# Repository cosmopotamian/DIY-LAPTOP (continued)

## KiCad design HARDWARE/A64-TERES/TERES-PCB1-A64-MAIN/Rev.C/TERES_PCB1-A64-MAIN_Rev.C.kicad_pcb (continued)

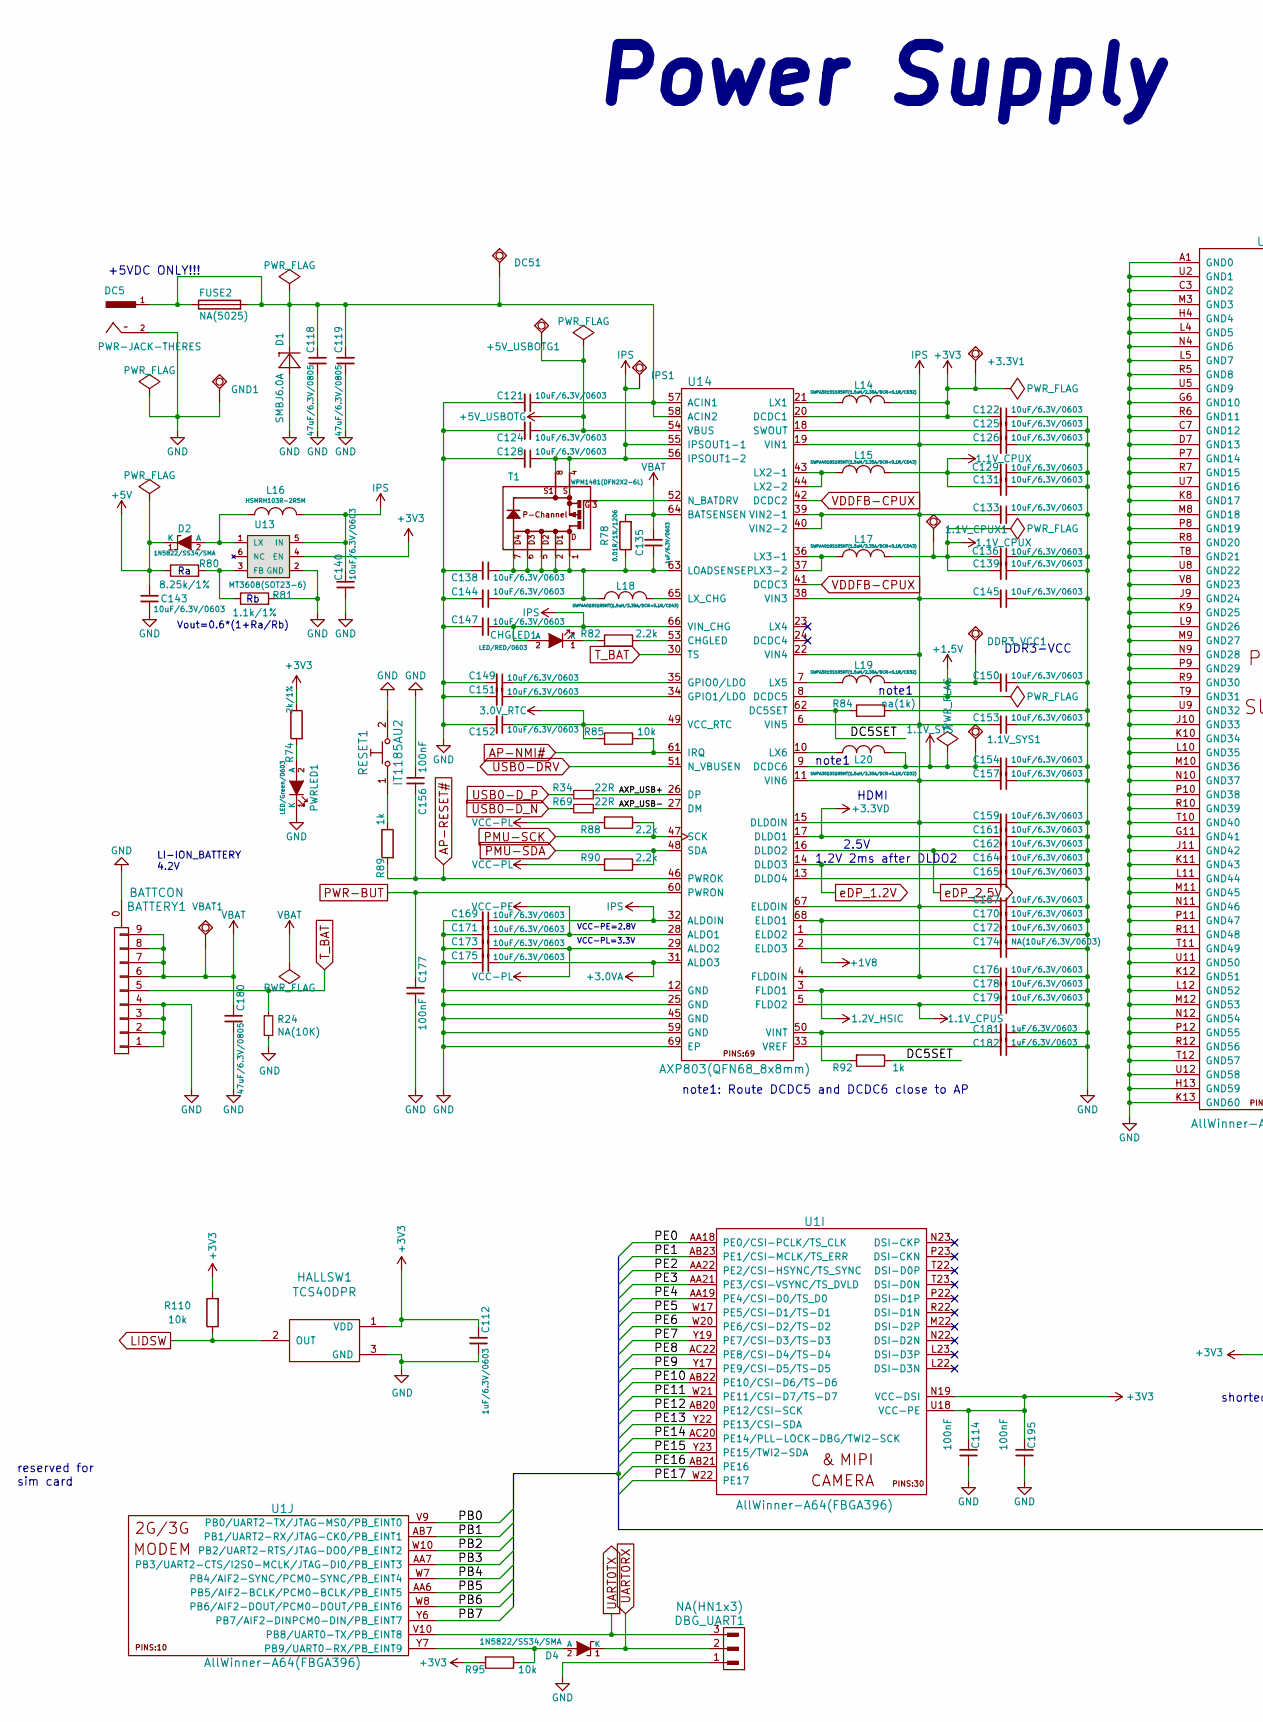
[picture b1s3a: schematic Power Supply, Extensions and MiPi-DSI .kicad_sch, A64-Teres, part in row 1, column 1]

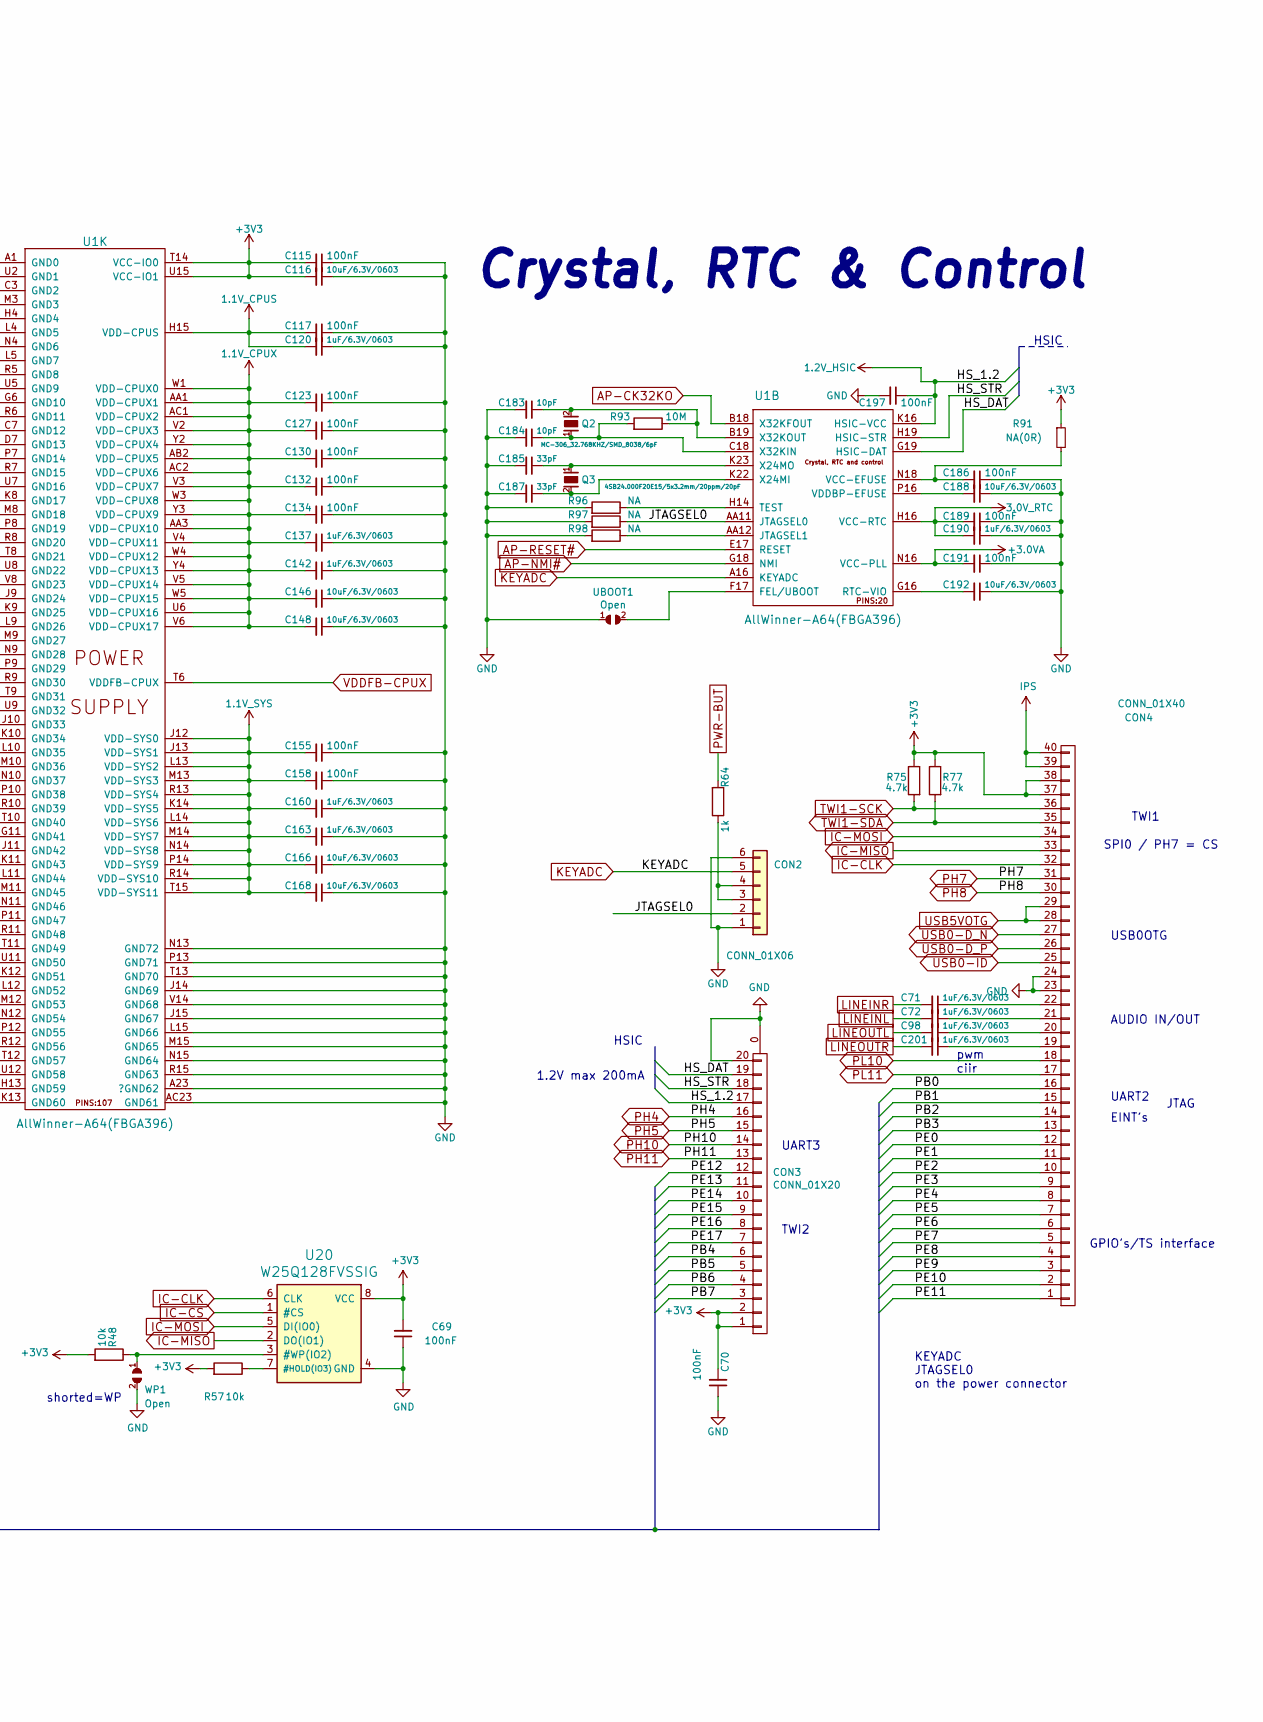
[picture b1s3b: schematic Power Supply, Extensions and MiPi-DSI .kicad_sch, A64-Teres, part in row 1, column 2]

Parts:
1.1V_CPUX1, 1.1V_SYS1: TESTPAD; TESTPAD_40-ROUND
+3.3V1: TESTPAD; TESTPAD_40-ROUND
+5V_USBOTG1: +5V_USBOTG; TESTPAD_40-ROUND
BATTERY1: BATTCON; BATCONN-TERES
C69, C70, C114, C115, C117, C123, C127, C130, C132, C134, C155, C156, C158, C177, C186, C189, C191, C195, C197: 100nF; C_0402_5MIL_DWS
C71, C72, C98, C112, C120, C135, C137, C142, C160, C163, C181, C182, C190, C201: 1uF/6.3V/0603; C_0603_5MIL_DWS
C116, C121, C122, C124, C125, C126, C128, C129, C131, C133, C136, C138, C139, C140, C143, C144, C145, C146, C147, C148, C149, C150, C151, C152, C153, C154, C157, C159, C161, C162, C164, C165, C166, C167, C168, C169, C170, C171, C172, C173, C175, C176, C178, C179, C188, C192: 10uF/6.3V/0603; C_0603_5MIL_DWS
C118, C119, C180: 47uF/6.3V/0805; C_0805_5MIL_DWS
C174: NA(10uF/6.3V/0603); C_0603_5MIL_DWS
C183, C184: 10pF; C_0402_5MIL_DWS
C185, C187: 33pF; C_0402_5MIL_DWS
CHGLED1: LED/RED/0603; LED_0603_KA
CON2: CONN_01X06; FLEXCON-0.5-6
CON3: CONN_01X20; FPV-WZA21-20-LF
CON4: CONN_01X40; FPV-WZA21-40-LF
D1: SMBJ6.0A; DO214AA
D2, D4: 1N5822/SS34/SMA; SMA-KA
DBG_UART1: NA(HN1x3); HN1x3(SMD)
DC5: PWR-JACK-THERES; DC-055-TERES
DC51: TESTPAD; TESTPAD_40-ROUND
DDR3_VCC1: TESTPAD; TESTPAD_40-ROUND
FUSE2: NA(5025); FUSE-5025
GND1: TESTPAD; TESTPAD_40-ROUND
HALLSW1: TCS40DPR; SOT23
IPS1: TESTPAD; TESTPAD_40-ROUND
L14, L19, L20: SWPA3015S1R5NT(1.5uH/2.30A/DCR<0.1R/CD32); CD32
L15, L17, L18: SWPA4018S1R5NT(1.5uH/3.35A/DCR<0.1R/CD43); CD42(43)
L16: HSMRH103R-2R5M; HSMRH103R
PWRLED1: LED/Green/0603; LED_0603_KA
Q2: MC-306_32.768KHZ/SMD_8038/6pF; MC306-HS
Q3: 4SB24.000F20E15/5x3.2mm/20ppm/20pF; Q5x3.25
R24: NA(10K); R_0402_5MIL_DWS
R34, R69: 22R; R_0402_5MIL_DWS
R48, R57, R85, R95, R110: 10k; R_0402_5MIL_DWS
R64, R89, R92: 1k; R_0402_5MIL_DWS
R74: 2k/1%; R_0402_5MIL_DWS
R75, R77: 4.7k; R_0402_5MIL_DWS
R78: 0.01R/1%/1206; R_1206_5MIL_DWS
R80: 8.25k/1%; R_0402_5MIL_DWS
R81: 1.1k/1%; R_0402_5MIL_DWS
R82, R88, R90: 2.2k; R_0402_5MIL_DWS
R84: na(1k); R_0402_5MIL_DWS
R91: NA(0R); R_0402_5MIL_DWS
R93: 10M; R_0402_5MIL_DWS
R96, R97, R98: NA; R_0402_5MIL_DWS
RESET1: IT1185AU2; uTACTIL
T1: WPM1481(DFN2X2-6L); DFN2x2-6L
U1: AllWinner-A64(FBGA396); FBGA396
U13: MT3608(SOT23-6); SOT23-6
U14: AXP803(QFN68_8x8mm); QFN68
U20: W25Q128FVSSIG; SO-8_208mil
UBOOT1: Open; SJ
VBAT1: TESTPAD; TESTPAD_40-ROUND
WP1: Open; SJ

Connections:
1.1V_CPUS: C117.2, C120.2, C179.2, U1.H15 (VDD-CPUS), U14.5 (FLDO2)
1.1V_CPUX: 1.1V_CPUX1.1, C123.2, C127.2, C129.2, C130.2, C131.2, C132.2, C134.2, C136.2, C137.2, C139.2, C142.2, C146.2, C148.2, L15.2, L17.2, U1.AA1 (VDD-CPUX1), U1.AA3 (VDD-CPUX10), U1.AB2 (VDD-CPUX5), U1.AC1 (VDD-CPUX2), U1.AC2 (VDD-CPUX6), U1.U6 (VDD-CPUX16), U1.V2 (VDD-CPUX3), U1.V3 (VDD-CPUX7), U1.V4 (VDD-CPUX11), U1.V5 (VDD-CPUX14), U1.V6 (VDD-CPUX17), U1.W1 (VDD-CPUX0), U1.W3 (VDD-CPUX8), U1.W4 (VDD-CPUX12), U1.W5 (VDD-CPUX15), U1.Y2 (VDD-CPUX4), U1.Y3 (VDD-CPUX9), U1.Y4 (VDD-CPUX13)
1.1V_SYS: 1.1V_SYS1.1, C154.2, C155.2, C158.2, C160.2, C163.2, C166.2, C168.2, L20.2, U1.J12 (VDD-SYS0), U1.J13 (VDD-SYS1), U1.K14 (VDD-SYS5), U1.L13 (VDD-SYS2), U1.L14 (VDD-SYS6), U1.M13 (VDD-SYS3), U1.M14 (VDD-SYS7), U1.N14 (VDD-SYS8), U1.P14 (VDD-SYS9), U1.R13 (VDD-SYS4), U1.R14 (VDD-SYS10), U1.T15 (VDD-SYS11), U14.9 (DCDC6)
1.2V_HSIC: C178.2, C197.1, CON3.17, U1.K16 (HSIC-VCC), U14.3 (FLDO1)
3.0V_RTC: C152.1, C189.2, C190.2, R85.2, U1.H16 (VCC-RTC), U14.49 (VCC_RTC)
+1.5V: C150.2, DDR3_VCC1.1, L19.2, U14.8 (DCDC5); also elsewhere on the board
+1V8: C170.2, U14.68 (ELDO1); also elsewhere on the board
+3.0VA: C175.1, C191.2, U1.N16 (VCC-PLL), U14.31 (ALDO3); also elsewhere on the board
+3.3VD: C161.2, U14.17 (DLDO1); also elsewhere on the board
+3V3: +3.3V1.1, C69.2, C70.2, C112.2, C114.2, C115.2, C116.2, C122.2, C195.2, CON3.1, CON3.2, CON4.37, CON4.38, HALLSW1.1 (VDD), L14.2, R48.2, R57.2, R74.1, R75.1, R77.1, R91.1, R95.2, R110.2, U1.N19 (VCC-DSI), U1.T14 (VCC-IO0), U1.U15 (VCC-IO1), U1.U18 (VCC-PE), U13.4 (EN), U14.20 (DCDC1), U20.8 (VCC); also elsewhere on the board
+5V: C143.2, D2.1 (K), R80.1; also elsewhere on the board
/Power Supply, Extensions and MiPi-DSI/AXP_USB+: R34.1, U14.26 (DP)
/Power Supply, Extensions and MiPi-DSI/AXP_USB-: R69.1, U14.27 (DM)
/Power Supply, Extensions and MiPi-DSI/DC5SET: R84.2, R92.1, U14.62 (DC5SET)
/Power Supply, Extensions and MiPi-DSI/HS_DAT: CON3.19, U1.G19 (HSIC-DAT)
/Power Supply, Extensions and MiPi-DSI/HS_STR: CON3.18, U1.H19 (HSIC-STR)
/Power Supply, Extensions and MiPi-DSI/JTAGSEL0: CON2.2, R97.1, U1.AA11 (JTAGSEL0)
/Power Supply, Extensions and MiPi-DSI/PB0: CON4.16, U1.V9 (PB0/UART2-TX/JTAG-MS0/PB_EINT0)
/Power Supply, Extensions and MiPi-DSI/PB1: CON4.15, U1.AB7 (PB1/UART2-RX/JTAG-CK0/PB_EINT1)
/Power Supply, Extensions and MiPi-DSI/PB2: CON4.14, U1.W10 (PB2/UART2-RTS/JTAG-DO0/PB_EINT2)
/Power Supply, Extensions and MiPi-DSI/PB3: CON4.13, U1.AA7 (PB3/UART2-CTS/I2S0-MCLK/JTAG-DI0/PB_EIN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)
/Power Supply, Extensions and MiPi-DSI/PB4: CON3.6, U1.W7 (PB4/AIF2-SYNC/PCM0-SYNC/PB_EINT4)
/Power Supply, Extensions and MiPi-DSI/PB5: CON3.5, U1.AA6 (PB5/AIF2-BCLK/PCM0-BCLK/PB_EINT5)
/Power Supply, Extensions and MiPi-DSI/PB6: CON3.4, U1.W8 (PB6/AIF2-DOUT/PCM0-DOUT/PB_EINT6)
/Power Supply, Extensions and MiPi-DSI/PB7: CON3.3, U1.Y6 (PB7/AIF2-DINPCM0-DIN/PB_EINT7)
/Power Supply, Extensions and MiPi-DSI/PE0: CON4.12, U1.AA18 (PE0/CSI-PCLK/TS_CLK)
/Power Supply, Extensions and MiPi-DSI/PE1: CON4.11, U1.AB23 (PE1/CSI-MCLK/TS_ERR)
/Power Supply, Extensions and MiPi-DSI/PE2: CON4.10, U1.AA22 (PE2/CSI-HSYNC/TS_SYNC)
/Power Supply, Extensions and MiPi-DSI/PE3: CON4.9, U1.AA21 (PE3/CSI-VSYNC/TS_DVLD)
/Power Supply, Extensions and MiPi-DSI/PE4: CON4.8, U1.AA19 (PE4/CSI-D0/TS_D0)
/Power Supply, Extensions and MiPi-DSI/PE5: CON4.7, U1.W17 (PE5/CSI-D1/TS-D1)
/Power Supply, Extensions and MiPi-DSI/PE6: CON4.6, U1.W20 (PE6/CSI-D2/TS-D2)
/Power Supply, Extensions and MiPi-DSI/PE7: CON4.5, U1.Y19 (PE7/CSI-D3/TS-D3)
/Power Supply, Extensions and MiPi-DSI/PE8: CON4.4, U1.AC22 (PE8/CSI-D4/TS-D4)
/Power Supply, Extensions and MiPi-DSI/PE9: CON4.3, U1.Y17 (PE9/CSI-D5/TS-D5)
/Power Supply, Extensions and MiPi-DSI/PE10: CON4.2, U1.AB22 (PE10/CSI-D6/TS-D6)
/Power Supply, Extensions and MiPi-DSI/PE11: CON4.1, U1.W21 (PE11/CSI-D7/TS-D7)
/Power Supply, Extensions and MiPi-DSI/PE12: CON3.12, U1.AB20 (PE12/CSI-SCK)
/Power Supply, Extensions and MiPi-DSI/PE13: CON3.11, U1.Y22 (PE13/CSI-SDA)
/Power Supply, Extensions and MiPi-DSI/PE14: CON3.10, U1.AC20 (PE14/PLL-LOCK-DBG/TWI2-SCK)
/Power Supply, Extensions and MiPi-DSI/PE15: CON3.9, U1.Y23 (PE15/TWI2-SDA)
/Power Supply, Extensions and MiPi-DSI/PE16: CON3.8, U1.AB21 (PE16)
/Power Supply, Extensions and MiPi-DSI/PE17: CON3.7, U1.W22 (PE17)
AP-CK32KO: U1.B18 (X32KFOUT); also elsewhere on the board
AP-NMI#: R85.1, U1.G18 (NMI), U14.61 (IRQ)
AP-RESET#: C156.2, R89.2, U1.E17 (RESET), U14.46 (PWROK)
GND: BATTERY1.0, BATTERY1.1, BATTERY1.2, BATTERY1.3, BATTERY1.4, C69.1, C70.1, C112.1, C114.1, C115.1, C116.1, C117.1, C118.1, C119.1, C120.1, C121.2, C122.1, C123.1, C124.2, C125.1, C126.1, C127.1, C128.2, C129.1, C130.1, C131.1, C132.1, C133.1, C134.1, C136.1, C137.1, C138.2, C139.1, C140.1, C142.1, C143.1, C144.2, C145.1, C146.1, C147.2, C148.1, C149.2, C150.1, C151.2, C152.2, C153.1, C154.1, C155.1, C156.1, C157.1, C158.1, C159.1, C160.1, C161.1, C162.1, C163.1, C164.1, C165.1, C166.1, C167.1, C168.1, C169.2, C170.1, C171.2, C172.1, C173.2, C174.1, C175.2, C176.1, C177.1, C178.1, C179.1, C180.1, C181.1, C182.1, C183.2, C184.2, C185.2, C186.1, C187.2, C188.1, C189.1, C190.1, C191.1, C192.1, C195.1, C197.2, CON2.0, CON2.1, CON2.6, CON3.0, CON3.20, CON4.0, CON4.23, CON4.24, D1.A, DBG_UART1.1, DC5.2 (-), GND1.1, HALLSW1.3 (GND), PWRLED1.1 (K), R24.2, R81.2, R84.1, R96.2, R97.2, R98.2, RESET1.2, U1.A1 (GND0), U1.A23 (?GND62), U1.AC23 (GND61), U1.C3 (GND2), U1.C7 (GND12), U1.D7 (GND13), U1.G6 (GND10), U1.G11 (GND41), U1.H4 (GND4), U1.H13 (GND59), U1.J9 (GND24), U1.J10 (GND33), U1.J11 (GND42), U1.J14 (GND69), U1.J15 (GND67), U1.K8 (GND17), U1.K9 (GND25), U1.K10 (GND34), U1.K11 (GND43), U1.K12 (GND51), U1.K13 (GND60), U1.L4 (GND5), U1.L5 (GND7), U1.L9 (GND26), U1.L10 (GND35), U1.L11 (GND44), U1.L12 (GND52), U1.L15 (GND66), U1.M3 (GND3), U1.M8 (GND18), U1.M9 (GND27), U1.M10 (GND36), U1.M11 (GND45), U1.M12 (GND53), U1.M15 (GND65), U1.N4 (GND6), U1.N9 (GND28), U1.N10 (GND37), U1.N11 (GND46), U1.N12 (GND54), U1.N13 (GND72), U1.N15 (GND64), U1.P7 (GND14), U1.P8 (GND19), U1.P9 (GND29), U1.P10 (GND38), U1.P11 (GND47), U1.P12 (GND55), U1.P13 (GND71), U1.R5 (GND8), U1.R6 (GND11), U1.R7 (GND15), U1.R8 (GND20), U1.R9 (GND30), U1.R10 (GND39), U1.R11 (GND48), U1.R12 (GND56), U1.R15 (GND63), U1.T8 (GND21), U1.T9 (GND31), U1.T10 (GND40), U1.T11 (GND49), U1.T12 (GND57), U1.T13 (GND70), U1.U2 (GND1), U1.U5 (GND9), U1.U7 (GND16), U1.U8 (GND22), U1.U9 (GND32), U1.U11 (GND50), U1.U12 (GND58), U1.V8 (GND23), U1.V14 (GND68), U13.2 (GND), U14.12 (GND), U14.25 (GND), U14.45 (GND), U14.59 (GND), U14.69 (EP), U20.4 (GND), UBOOT1.1, WP1.2; also elsewhere on the board
IC-CLK: CON4.32, U20.6 (CLK); also elsewhere on the board
IC-CS: U20.1 (#CS); also elsewhere on the board
IC-MISO: CON4.33, U20.2 (DO(IO1)); also elsewhere on the board
IC-MOSI: CON4.34, U20.5 (DI(IO0)); also elsewhere on the board
IPS: C126.2, C128.1, C133.2, C140.2, C145.2, C147.1, C153.2, C157.2, C159.2, C167.2, C169.1, C176.2, CHGLED1.2 (A), CON4.39, CON4.40, IPS1.1, L16.1, T1.4 (S), T1.8 (S1), U13.5 (IN), U14.4 (FLDOIN), U14.6 (VIN5), U14.11 (VIN6), U14.15 (DLDOIN), U14.19 (VIN1), U14.22 (VIN4), U14.32 (ALDOIN), U14.38 (VIN3), U14.39 (VIN2-1), U14.40 (VIN2-2), U14.55 (IPSOUT1-1), U14.56 (IPSOUT1-2), U14.66 (VIN_CHG), U14.67 (ELDOIN); also elsewhere on the board
KEYADC: CON2.5, U1.A16 (KEYADC)
LIDSW: HALLSW1.2 (OUT), R110.1; also elsewhere on the board
LINEINL: C72.2; also elsewhere on the board
LINEINR: C71.2; also elsewhere on the board
LINEOUTL: C98.2; also elsewhere on the board
LINEOUTR: C201.2; also elsewhere on the board
unnamed: C71.1, CON4.22
unnamed: C72.1, CON4.21
unnamed: C98.1, CON4.20
unnamed: C118.2, C119.2, C121.1, D1.C, DC5.1 (+), DC51.1, FUSE2.1, FUSE2.2, U14.57 (ACIN1), U14.58 (ACIN2)
unnamed: C125.2, U14.18 (SWOUT)
unnamed: C135.1, C138.1, C144.1, L18.1, R78.1, T1.1 (D), T1.2 (D1), T1.5 (D2), T1.6 (D3), T1.7 (D4), U14.63 (LOADSENSEP)
unnamed: C149.1, U14.35 (GPIO0/LDO)
unnamed: C151.1, U14.34 (GPIO1/LDO)
unnamed: C165.2, U14.13 (DLDO4)
unnamed: C172.2, U14.1 (ELDO2)
unnamed: C174.2, U14.2 (ELDO3)
unnamed: C181.2, R92.2, U14.50 (VINT)
unnamed: C182.2, U14.33 (VREF)
unnamed: C183.1, Q2.2, R93.1, U1.B19 (X32KOUT)
unnamed: C184.1, Q2.1, R93.2, U1.C18 (X32KIN)
unnamed: C185.1, Q3.1, U1.K23 (X24MO)
unnamed: C186.2, R91.2, U1.N18 (VCC-EFUSE)
unnamed: C187.1, Q3.2, U1.K22 (X24MI)
unnamed: C188.2, U1.P16 (VDDBP-EFUSE)
unnamed: C192.2, U1.G16 (RTC-VIO)
unnamed: C201.1, CON4.19
unnamed: CHGLED1.1 (K), R82.2
unnamed: CON2.3, CON2.4, R64.1
unnamed: D2.2 (A), L16.2, U13.1 (LX)
unnamed: D4.2 (A), R95.1, U1.Y7 (PB9/UART0-RX/PB_EINT9)
unnamed: L14.1, U14.21 (LX1)
unnamed: L15.1, U14.43 (LX2-1), U14.44 (LX2-2)
unnamed: L17.1, U14.36 (LX3-1), U14.37 (LX3-2)
unnamed: L18.2, U14.65 (LX_CHG)
unnamed: L19.1, U14.7 (LX5)
unnamed: L20.1, U14.10 (LX6)
unnamed: PWRLED1.2 (A), R74.2
unnamed: R48.1, U20.3 (#WP(IO2)), WP1.1
unnamed: R57.1, U20.7 (#HOLD(IO3))
unnamed: R80.2, R81.1, U13.3 (FB)
unnamed: R82.1, U14.53 (CHGLED)
unnamed: R89.1, RESET1.1
unnamed: R96.1, U1.H14 (TEST)
unnamed: R98.1, U1.AA12 (JTAGSEL1)
unnamed: T1.3 (G), U14.52 (N_BATDRV)
unnamed: U1.F17 (FEL/UBOOT), UBOOT1.2
PH4: CON3.16; also elsewhere on the board
PH5: CON3.15; also elsewhere on the board
PH7: CON4.31; also elsewhere on the board
PH8: CON4.30; also elsewhere on the board
PH10: CON3.14; also elsewhere on the board
PH11: CON3.13; also elsewhere on the board
PL10: CON4.18; also elsewhere on the board
PL11: CON4.17; also elsewhere on the board
PMU-SCK: R88.1, U14.47 (SCK); also elsewhere on the board
PMU-SDA: R90.1, U14.48 (SDA); also elsewhere on the board
PWR-BUT: C177.2, R64.2, U14.60 (PWRON)
TWI1-SCK: CON4.36, R75.2; also elsewhere on the board
TWI1-SDA: CON4.35, R77.2; also elsewhere on the board
T_BAT: BATTERY1.5, R24.1, U14.30 (TS)
UART0RX: D4.1 (K), DBG_UART1.2; also elsewhere on the board
UART0TX: DBG_UART1.3, U1.V10 (PB8/UART0-TX/PB_EINT8); also elsewhere on the board
USB0-DRV: U14.51 (N_VBUSEN); also elsewhere on the board
USB0-D_N: CON4.27, R69.2; also elsewhere on the board
USB0-D_P: CON4.26, R34.2; also elsewhere on the board
USB0-ID: CON4.25; also elsewhere on the board
USB5VOTG: +5V_USBOTG1.1, C124.1, CON4.28, CON4.29, U14.54 (VBUS); also elsewhere on the board
VBAT: BATTERY1.6, BATTERY1.7, BATTERY1.8, BATTERY1.9, C135.2, C180.2, R78.2, U14.64 (BATSENSEN), VBAT1.1
VCC-PE: C171.1, U14.28 (ALDO1)
VCC-PL: C173.1, R88.2, R90.2, U14.29 (ALDO2); also elsewhere on the board
VDDFB-CPUX: U1.T6 (VDDFB-CPUX), U14.41 (DCDC3), U14.42 (DCDC2)
eDP_1.2V: C164.2, U14.14 (DLDO3); also elsewhere on the board
eDP_2.5V: C162.2, U14.16 (DLDO2); also elsewhere on the board

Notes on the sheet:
USB0OTG
DDR3-VCC
note1
HSIC
reserved for sim card
AUDIO IN/OUT
LI-ION_BATTERY 4.2V
1.2V max 200mA
UART2
VCC-PE=2.8V
Crystal, RTC & Control
KEYADC JTAGSEL0 on the power connector
UART3
ciir
note1: Route DCDC5 and DCDC6 close to AP
JTAG
TWI2
Power Supply
pwm
shorted=WP
1.2V 2ms after DLDO2
SPI0 / PH7 = CS
Vout=0.6*(1+Ra/Rb)
HDMI
GPIO's/TS interface
TWI1
2.5V
VCC-PL=3.3V
EINT's
+5VDC ONLY!!!

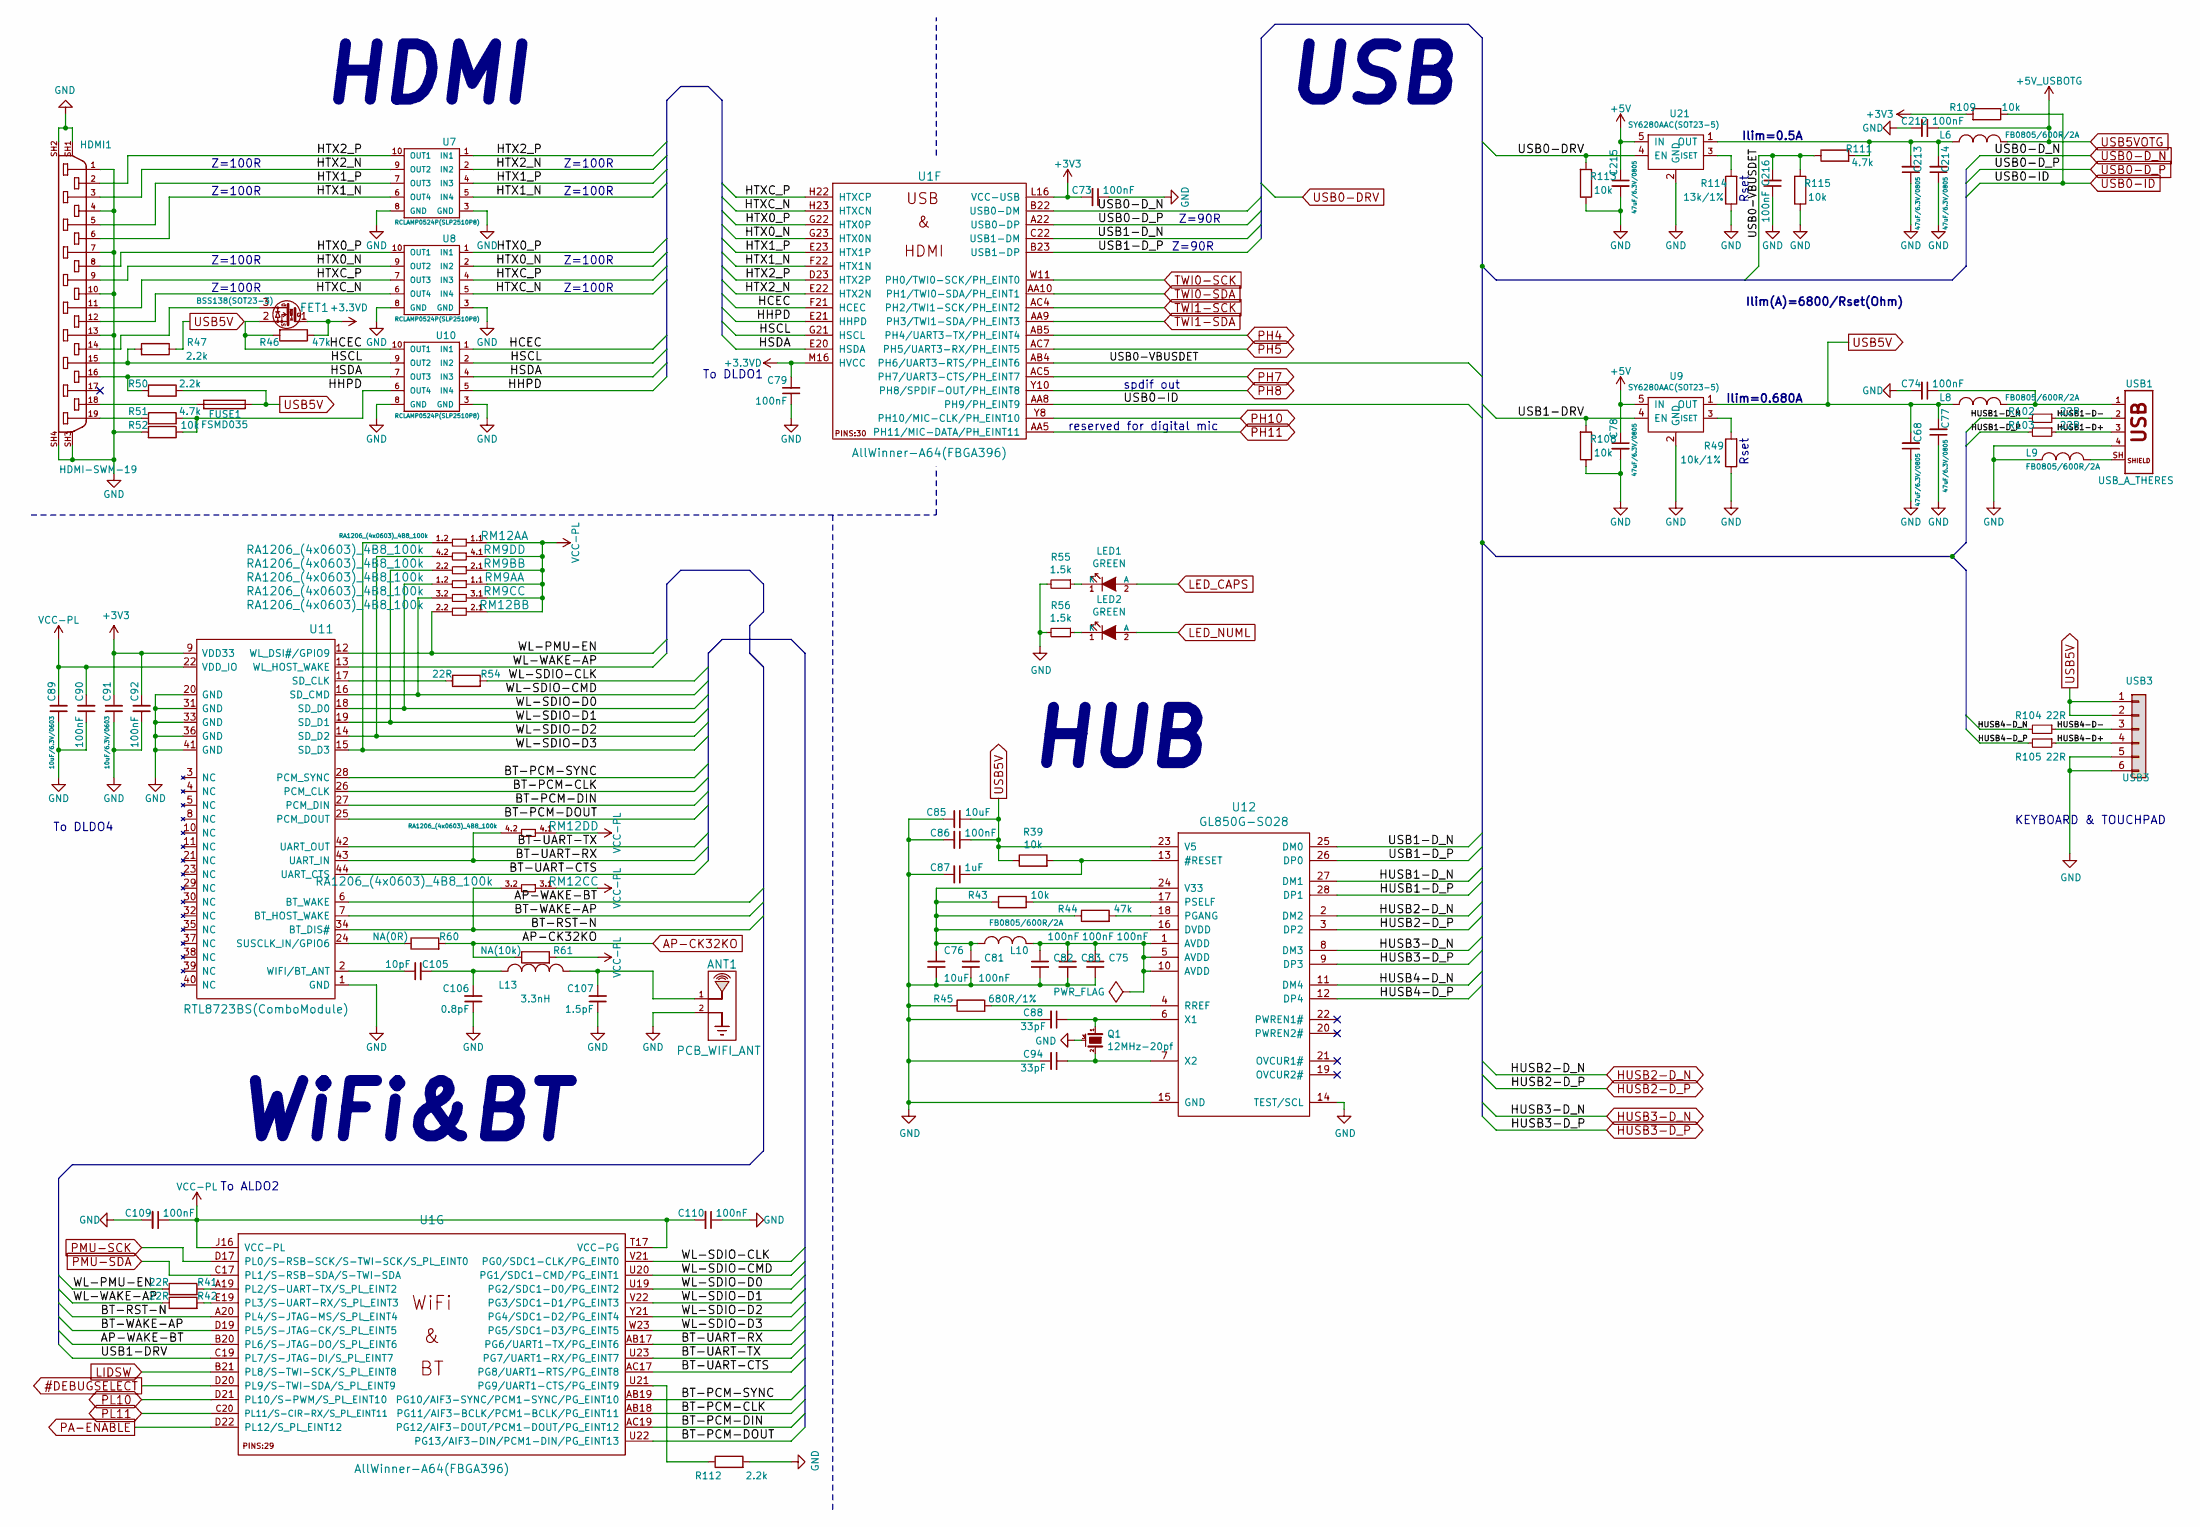
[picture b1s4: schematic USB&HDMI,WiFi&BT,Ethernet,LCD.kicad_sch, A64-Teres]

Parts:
ANT1: PCB_WIFI_ANT; U.FL-R-SMT-1
C68, C77, C78, C213, C214, C215: 47uF/6.3V/0805; C_0805_5MIL_DWS
C73, C74, C75, C79, C81, C82, C83, C86, C90, C92, C109, C110, C212, C216: 100nF; C_0402_5MIL_DWS
C76: 10uF; C_0603_5MIL_DWS
C85: 10uF; R_0603_5MIL_DWS
C87: 1uF; C_0603_5MIL_DWS
C88, C94: 33pF; C_0402_5MIL_DWS
C89, C91: 10uF/6.3V/0603; C_0603_5MIL_DWS
C105: 10pF; C_0402_5MIL_DWS
C106: 0.8pF; C_0402_5MIL_DWS
C107: 1.5pF; C_0402_5MIL_DWS
FET1: BSS138(SOT23-3); SOT23
FUSE1: FSMD035; FUSE-1206
HDMI1: HDMI-SWM-19; HDMI-MINI-TERES
L6, L8, L9, L10: FB0805/600R/2A; L_0805_5MIL_DWS
L13: 3.3nH; R_0402_5MIL_DWS
LED1, LED2: GREEN; LED_0603_KA
Q1: 12MHz-20pf; TSX-3.2x2.5mm_GND(3)
R39, R43, R52, R108, R109, R113, R115: 10k; R_0402_5MIL_DWS
R41, R42, R54, R102, R103, R104, R105: 22R; R_0402_5MIL_DWS
R44, R46: 47k; R_0402_5MIL_DWS
R45: 680R/1%; R_0603_5MIL_DWS
R47, R50, R112: 2.2k; R_0402_5MIL_DWS
R49: 10k/1%; R_0402_5MIL_DWS
R51, R111: 4.7k; R_0402_5MIL_DWS
R55, R56: 1.5k; R_0402_5MIL_DWS
R60: NA(0R); R_0402_5MIL_DWS
R61: NA(10k); R_0402_5MIL_DWS
R114: 13k/1%; R_0402_5MIL_DWS
RM9A, RM9B, RM12A, RM12B: RA1206_(4x0603)_4B8_100k; R_MATRIX_4
RM9C, RM9D, RM12C, RM12D: RA1206_(4x0603)_4B8_100k; RA1206_(4X0603)_4B8_xx
U1: AllWinner-A64(FBGA396); FBGA396
U7, U8, U10: RCLAMP0524P(SLP2510P8); SLP2510P8
U9, U21: SY6280AAC(SOT23-5); SOT-23-5
U11: RTL8723BS(ComboModule); RL-SM02BD(RTL8723BS)
U12: GL850G-SO28; SSOP28
USB1: USB_A_THERES; USB-A-TERES
USB3: USB3; FLEXCON-0.5-6

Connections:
#DEBUGSELECT: U1.D20 (PL9/S-TWI-SDA/S_PL_EINT9); also elsewhere on the board
+3.3VD: C79.2, FET1.1 (G), R46.1, U1.M16 (HVCC); also elsewhere on the board
+3V3: C73.2, C91.2, C92.2, R109.2, U1.L16 (VCC-USB), U11.9 (VDD33); also elsewhere on the board
+5V: C78.1, C215.1, U9.5 (IN), U21.5 (IN); also elsewhere on the board
/USB&HDMI,WiFi&BT,Ethernet,LCD/AP-WAKE-BT: U1.B20 (PL6/S-JTAG-DO/S_PL_EINT6), U11.6 (BT_WAKE)
/USB&HDMI,WiFi&BT,Ethernet,LCD/BT-PCM-CLK: U1.AB18 (PG11/AIF3-BCLK/PCM1-BCLK/PG_EINT11), U11.26 (PCM_CLK)
/USB&HDMI,WiFi&BT,Ethernet,LCD/BT-PCM-DIN: U1.AC19 (PG12/AIF3-DOUT/PCM1-DOUT/PG_EINT12), U11.27 (PCM_DIN)
/USB&HDMI,WiFi&BT,Ethernet,LCD/BT-PCM-DOUT: U1.U22 (PG13/AIF3-DIN/PCM1-DIN/PG_EINT13), U11.25 (PCM_DOUT)
/USB&HDMI,WiFi&BT,Ethernet,LCD/BT-PCM-SYNC: U1.AB19 (PG10/AIF3-SYNC/PCM1-SYNC/PG_EINT10), U11.28 (PCM_SYNC)
/USB&HDMI,WiFi&BT,Ethernet,LCD/BT-RST-N: RM12C.3.2, U1.A20 (PL4/S-JTAG-MS/S_PL_EINT4), U11.34 (BT_DIS#); also elsewhere on the board
/USB&HDMI,WiFi&BT,Ethernet,LCD/BT-UART-CTS: U1.AC17 (PG8/UART1-RTS/PG_EINT8), U11.44 (UART_CTS)
/USB&HDMI,WiFi&BT,Ethernet,LCD/BT-UART-RX: RM12D.4.2, U1.AB17 (PG6/UART1-TX/PG_EINT6), U11.43 (UART_IN); also elsewhere on the board
/USB&HDMI,WiFi&BT,Ethernet,LCD/BT-UART-TX: U1.U23 (PG7/UART1-RX/PG_EINT7), U11.42 (UART_OUT)
/USB&HDMI,WiFi&BT,Ethernet,LCD/BT-WAKE-AP: U1.D19 (PL5/S-JTAG-CK/S_PL_EINT5), U11.7 (BT_HOST_WAKE)
/USB&HDMI,WiFi&BT,Ethernet,LCD/HCEC: FET1.2 (S), R46.2, U1.F21 (HCEC), U10.1 (IN1), U10.10 (OUT1)
/USB&HDMI,WiFi&BT,Ethernet,LCD/HHPD: R51.1, R52.1, U1.E21 (HHPD), U10.5 (IN4), U10.6 (OUT4)
/USB&HDMI,WiFi&BT,Ethernet,LCD/HSCL: HDMI1.15, R47.2, U1.G21 (HSCL), U10.2 (IN2), U10.9 (OUT2)
/USB&HDMI,WiFi&BT,Ethernet,LCD/HSDA: HDMI1.16, R50.2, U1.E20 (HSDA), U10.4 (IN3), U10.7 (OUT3)
/USB&HDMI,WiFi&BT,Ethernet,LCD/HTX0_N: HDMI1.9, U1.G23 (HTX0N), U8.2 (IN2), U8.9 (OUT2)
/USB&HDMI,WiFi&BT,Ethernet,LCD/HTX0_P: HDMI1.8, U1.G22 (HTX0P), U8.1 (IN1), U8.10 (OUT1)
/USB&HDMI,WiFi&BT,Ethernet,LCD/HTX1_N: HDMI1.6, U1.F22 (HTX1N), U7.5 (IN4), U7.6 (OUT4)
/USB&HDMI,WiFi&BT,Ethernet,LCD/HTX1_P: HDMI1.5, U1.E23 (HTX1P), U7.4 (IN3), U7.7 (OUT3)
/USB&HDMI,WiFi&BT,Ethernet,LCD/HTX2_N: HDMI1.3, U1.E22 (HTX2N), U7.2 (IN2), U7.9 (OUT2)
/USB&HDMI,WiFi&BT,Ethernet,LCD/HTX2_P: HDMI1.2, U1.D23 (HTX2P), U7.1 (IN1), U7.10 (OUT1)
/USB&HDMI,WiFi&BT,Ethernet,LCD/HTXC_N: HDMI1.12, U1.H23 (HTXCN), U8.5 (IN4), U8.6 (OUT4)
/USB&HDMI,WiFi&BT,Ethernet,LCD/HTXC_P: HDMI1.11, U1.H22 (HTXCP), U8.4 (IN3), U8.7 (OUT3)
/USB&HDMI,WiFi&BT,Ethernet,LCD/HUSB1-D+: R103.1, USB1.3
/USB&HDMI,WiFi&BT,Ethernet,LCD/HUSB1-D-: R102.1, USB1.2
/USB&HDMI,WiFi&BT,Ethernet,LCD/HUSB1-D_N: R102.2, U12.27 (DM1)
/USB&HDMI,WiFi&BT,Ethernet,LCD/HUSB1-D_P: R103.2, U12.28 (DP1)
/USB&HDMI,WiFi&BT,Ethernet,LCD/HUSB4-D+: R105.1, USB3.4
/USB&HDMI,WiFi&BT,Ethernet,LCD/HUSB4-D-: R104.1, USB3.3
/USB&HDMI,WiFi&BT,Ethernet,LCD/HUSB4-D_N: R104.2, U12.11 (DM4)
/USB&HDMI,WiFi&BT,Ethernet,LCD/HUSB4-D_P: R105.2, U12.12 (DP4)
/USB&HDMI,WiFi&BT,Ethernet,LCD/USB0-VBUSDET: C216.2, R111.1, R115.2, U1.AB4 (PH6/UART3-RTS/PH_EINT6)
/USB&HDMI,WiFi&BT,Ethernet,LCD/USB1-DRV: R108.2, U1.C19 (PL7/S-JTAG-DI/S_PL_EINT7), U9.4 (EN)
/USB&HDMI,WiFi&BT,Ethernet,LCD/USB1-D_N: U1.C22 (USB1-DM), U12.25 (DM0)
/USB&HDMI,WiFi&BT,Ethernet,LCD/USB1-D_P: U1.B23 (USB1-DP), U12.26 (DP0)
/USB&HDMI,WiFi&BT,Ethernet,LCD/WL-PMU-EN: R41.1, RM12B.2.2, U11.12 (WL_DSI#/GPIO9); also elsewhere on the board
/USB&HDMI,WiFi&BT,Ethernet,LCD/WL-SDIO-CLK: R54.2, U1.V21 (PG0/SDC1-CLK/PG_EINT0)
/USB&HDMI,WiFi&BT,Ethernet,LCD/WL-SDIO-CMD: RM9C.3.2, U1.U20 (PG1/SDC1-CMD/PG_EINT1), U11.16 (SD_CMD); also elsewhere on the board
/USB&HDMI,WiFi&BT,Ethernet,LCD/WL-SDIO-D0: RM9A.1.2, U1.U19 (PG2/SDC1-D0/PG_EINT2), U11.18 (SD_D0); also elsewhere on the board
/USB&HDMI,WiFi&BT,Ethernet,LCD/WL-SDIO-D1: RM9B.2.2, U1.V22 (PG3/SDC1-D1/PG_EINT3), U11.19 (SD_D1); also elsewhere on the board
/USB&HDMI,WiFi&BT,Ethernet,LCD/WL-SDIO-D2: RM9D.4.2, U1.Y21 (PG4/SDC1-D2/PG_EINT4), U11.14 (SD_D2); also elsewhere on the board
/USB&HDMI,WiFi&BT,Ethernet,LCD/WL-SDIO-D3: RM12A.1.2, U1.W23 (PG5/SDC1-D3/PG_EINT5), U11.15 (SD_D3); also elsewhere on the board
/USB&HDMI,WiFi&BT,Ethernet,LCD/WL-WAKE-AP: R42.1, U11.13 (WL_HOST_WAKE)
AP-CK32KO: R60.2, R61.1; also elsewhere on the board
GND: ANT1.2, C68.1, C73.1, C74.2, C75.2, C76.2, C77.1, C78.2, C79.1, C81.2, C82.2, C83.2, C85.1, C86.2, C87.2, C88.2, C89.1, C90.1, C91.1, C92.1, C94.2, C106.1, C107.1, C109.2, C110.1, C212.2, C213.1, C214.1, C215.2, C216.1, HDMI1.0, HDMI1.1, HDMI1.4, HDMI1.7, HDMI1.10, HDMI1.13, HDMI1.SH1 (20), HDMI1.SH2 (21), HDMI1.SH3 (22), HDMI1.SH4 (23), L9.1, Q1.3 (case), R45.1, R49.1, R52.2, R55.2, R56.2, R108.1, R112.2, R113.1, R114.1, R115.1, U7.3 (GND), U7.8 (GND), U8.3 (GND), U8.8 (GND), U9.2 (GND), U10.3 (GND), U10.8 (GND), U11.1 (GND), U11.20 (GND), U11.31 (GND), U11.33 (GND), U11.36 (GND), U11.41 (GND), U12.14 (TEST/SCL), U12.15 (GND), U21.2 (GND), USB1.4, USB3.0, USB3.5, USB3.6; also elsewhere on the board
HUSB2-D_N: U12.2 (DM2); also elsewhere on the board
HUSB2-D_P: U12.3 (DP2); also elsewhere on the board
HUSB3-D_N: U12.8 (DM3); also elsewhere on the board
HUSB3-D_P: U12.9 (DP3); also elsewhere on the board
LED_CAPS: LED1.2 (A); also elsewhere on the board
LED_NUML: LED2.2 (A); also elsewhere on the board
LIDSW: U1.B21 (PL8/S-TWI-SCK/S_PL_EINT8); also elsewhere on the board
unnamed: ANT1.1, C107.2, L13.2
unnamed: C74.1, L8.2, USB1.1
unnamed: C75.1, C82.1, C83.1, L10.2, U12.1 (AVDD), U12.5 (AVDD), U12.10 (AVDD)
unnamed: C76.1, C81.1, L10.1, R43.1, R44.1, U12.16 (DVDD), U12.24 (V33)
unnamed: C87.1, R39.2, U12.13 (#RESET)
unnamed: C88.1, Q1.1, U12.6 (X1)
unnamed: C94.1, Q1.2, U12.7 (X2)
unnamed: C105.1, U11.2 (WIFI/BT_ANT)
unnamed: C105.2, C106.2, L13.1
unnamed: C213.2, C214.2, L6.1, R111.2, U21.1 (OUT)
unnamed: FET1.3 (D), HDMI1.14
unnamed: FUSE1.2, HDMI1.18
unnamed: HDMI1.19, R51.2
unnamed: L9.2, USB1.0, USB1.SH (5)
unnamed: LED1.1 (K), R55.1
unnamed: LED2.1 (K), R56.1
unnamed: R41.2, U1.A19 (PL2/S-UART-TX/S_PL_EINT2)
unnamed: R42.2, U1.E19 (PL3/S-UART-RX/S_PL_EINT3)
unnamed: R43.2, U12.17 (PSELF)
unnamed: R44.2, U12.18 (PGANG)
unnamed: R45.2, U12.4 (RREF)
unnamed: R49.2, U9.3 (ISET)
unnamed: R54.1, U11.17 (SD_CLK)
unnamed: R60.1, U11.24 (SUSCLK_IN/GPIO6)
unnamed: R112.1, U1.U21 (PG9/UART1-CTS/PG_EINT9)
unnamed: R114.2, U21.3 (ISET)
PA-ENABLE: U1.D22 (PL12/S_PL_EINT12); also elsewhere on the board
PH4: U1.AB5 (PH4/UART3-TX/PH_EINT4); also elsewhere on the board
PH5: U1.AC7 (PH5/UART3-RX/PH_EINT5); also elsewhere on the board
PH7: U1.AC5 (PH7/UART3-CTS/PH_EINT7); also elsewhere on the board
PH8: U1.Y10 (PH8/SPDIF-OUT/PH_EINT8); also elsewhere on the board
PH10: U1.Y8 (PH10/MIC-CLK/PH_EINT10); also elsewhere on the board
PH11: U1.AA5 (PH11/MIC-DATA/PH_EINT11); also elsewhere on the board
PL10: U1.D21 (PL10/S-PWM/S_PL_EINT10); also elsewhere on the board
PL11: U1.C20 (PL11/S-CIR-RX/S_PL_EINT11); also elsewhere on the board
PMU-SCK: U1.D17 (PL0/S-RSB-SCK/S-TWI-SCK/S_PL_EINT0); also elsewhere on the board
PMU-SDA: U1.C17 (PL1/S-RSB-SDA/S-TWI-SDA); also elsewhere on the board
TWI0-SCK: U1.W11 (PH0/TWI0-SCK/PH_EINT0); also elsewhere on the board
TWI0-SDA: U1.AA10 (PH1/TWI0-SDA/PH_EINT1); also elsewhere on the board
TWI1-SCK: U1.AC4 (PH2/TWI1-SCK/PH_EINT2); also elsewhere on the board
TWI1-SDA: U1.AA9 (PH3/TWI1-SDA/PH_EINT3); also elsewhere on the board
USB0-DRV: R113.2, U21.4 (EN); also elsewhere on the board
USB0-D_N: U1.B22 (USB0-DM); also elsewhere on the board
USB0-D_P: U1.A22 (USB0-DP); also elsewhere on the board
USB0-ID: R109.1, U1.AA8 (PH9/PH_EINT9); also elsewhere on the board
USB5V: C68.2, C77.2, C85.2, C86.1, FUSE1.1, L8.1, R39.1, R47.1, R50.1, U9.1 (OUT), U12.23 (V5), USB3.1, USB3.2; also elsewhere on the board
USB5VOTG: C212.1, L6.2; also elsewhere on the board
VCC-PL: C89.2, C90.2, C109.1, C110.2, R61.2, RM9A.1.1, RM9B.2.1, RM9C.3.1, RM9D.4.1, RM12A.1.1, RM12B.2.1, RM12C.3.1, RM12D.4.1, U1.J16 (VCC-PL), U1.T17 (VCC-PG), U11.22 (VDD_IO); also elsewhere on the board

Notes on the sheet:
Z=100R
Rset
Ilim=0.680A
reserved for digital mic
WiFi&BT
HDMI
To ALDO2
USB
To DLDO4
Ilim=0.5A
HUB
Ilim(A)=6800/Rset(Ohm)
To DLDO1
Z=90R
spdif out
KEYBOARD & TOUCHPAD
